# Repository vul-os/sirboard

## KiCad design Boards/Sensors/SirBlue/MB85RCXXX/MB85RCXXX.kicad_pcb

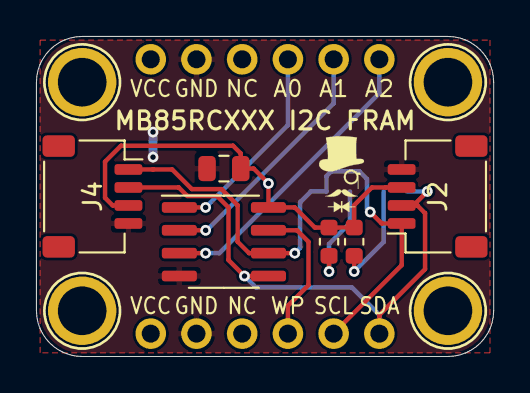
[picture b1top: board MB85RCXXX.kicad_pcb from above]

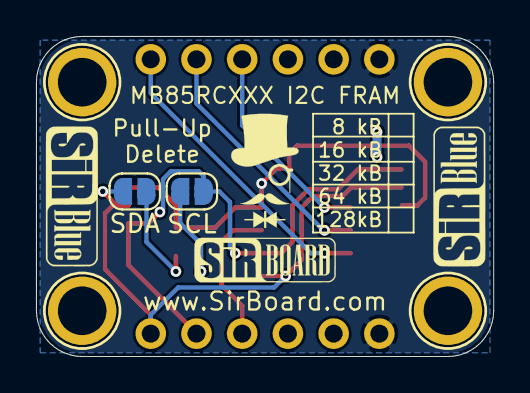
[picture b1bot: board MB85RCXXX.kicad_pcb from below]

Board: 2 copper layers, 25.4 x 17.8 mm, 14 parts (4 on the bottom side), 10 nets.

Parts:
C1: 10uF; C_0805_2012Metric
H1, H2, H3, H4: MountingHole; MountingHole_M2.5_SirBoard
J1, J3: Conn_01x06; PinHeader_1x06_P2.54mm_Vertical
J2, J4: Conn_01x04; JST_SH_SM04B-SRSS-TB_1x04-1MP_P1.00mm_Horizontal
R1, R2: 10K; R_0603_1608Metric
SCL: SolderJumper_2_Open; SolderJumper-2_P1.3mm_Open_RoundedPad1.0x1.5mm
SDA: SolderJumper_2_Open; SolderJumper-2_P1.3mm_Open_RoundedPad1.0x1.5mm
U1: MB85RCXXX; SOIC-8_3.9x4.9mm_P1.27mm

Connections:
A0: J3.4, U1.1
A1: J3.5, U1.2
A2: J3.6, U1.3
GND: C1.2, J1.2, J2.4, J3.2, J4.4, U1.4
unnamed: R1.2, SCL.2
unnamed: R2.2, SDA.2
SCL: J1.5, J2.1, J4.1, SCL.1, U1.6
SDA: J1.6, J2.2, J4.2, SDA.1, U1.5
VCC: C1.1, J1.1, J2.3, J3.1, J4.3, R1.1, R2.1, U1.8
WP: J1.4, U1.7

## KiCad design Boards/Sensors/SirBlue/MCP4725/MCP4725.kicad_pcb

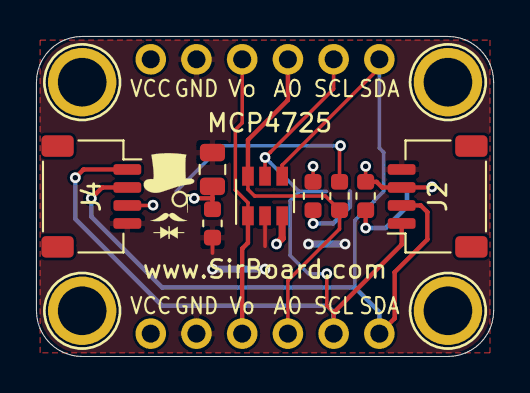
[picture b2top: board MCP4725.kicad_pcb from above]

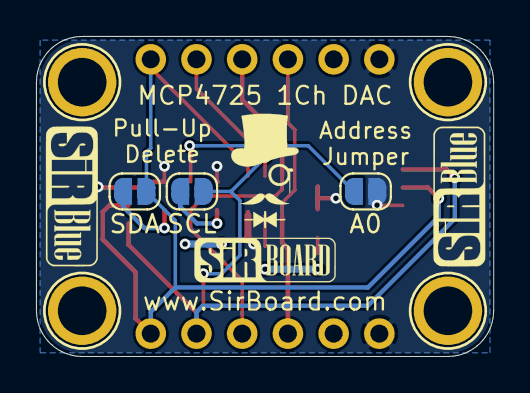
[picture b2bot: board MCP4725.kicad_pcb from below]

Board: 2 copper layers, 25.4 x 17.8 mm, 17 parts (5 on the bottom side), 9 nets.

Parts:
A0: SolderJumper_2_Open; SolderJumper-2_P1.3mm_Open_RoundedPad1.0x1.5mm
C1: 10uF; C_0805_2012Metric
C5: 100nF; C_0603_1608Metric
H1, H2, H3, H4: MountingHole; MountingHole_M2.5_SirBoard
J1, J3: Conn_01x06; PinHeader_1x06_P2.54mm_Vertical
J2, J4: Conn_01x04; JST_SH_SM04B-SRSS-TB_1x04-1MP_P1.00mm_Horizontal
R1, R2, R3: 10K; R_0603_1608Metric
SCL: SolderJumper_2_Open; SolderJumper-2_P1.3mm_Open_RoundedPad1.0x1.5mm
SDA: SolderJumper_2_Open; SolderJumper-2_P1.3mm_Open_RoundedPad1.0x1.5mm
U1: MCP4725; SOT-23-6

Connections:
A0: J1.4, J3.4, R3.2, U1.6
GND: C1.2, C5.2, J1.2, J2.4, J3.2, J4.4, U1.2
unnamed: A0.2, R3.1
unnamed: R1.2, SCL.2
unnamed: R2.2, SDA.2
SCL: J1.5, J2.1, J3.5, J4.1, SCL.1, U1.5
SDA: J1.6, J2.2, J3.6, J4.2, SDA.1, U1.4
VCC: A0.1, C1.1, C5.1, J1.1, J2.3, J3.1, J4.3, R1.1, R2.1, U1.3
Vout: J1.3, J3.3, U1.1

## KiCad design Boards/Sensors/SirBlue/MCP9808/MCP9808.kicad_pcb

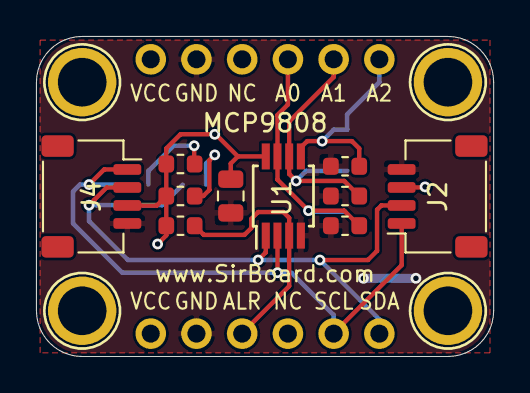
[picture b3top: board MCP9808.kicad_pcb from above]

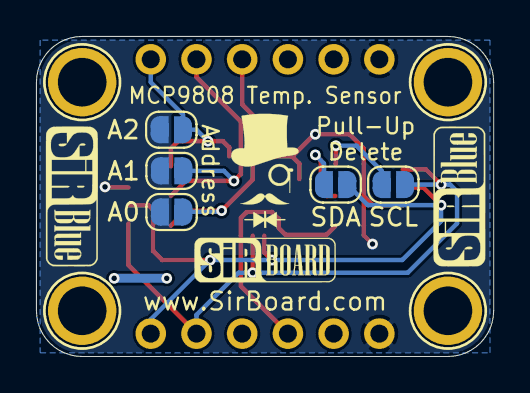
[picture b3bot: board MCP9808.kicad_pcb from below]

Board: 2 copper layers, 25.4 x 17.8 mm, 21 parts (7 on the bottom side), 10 nets.

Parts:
A0, A1, A2: SolderJumper_2_Open; SolderJumper-2_P1.3mm_Open_RoundedPad1.0x1.5mm
C1: 10uF; C_0805_2012Metric
H1, H2, H3, H4: MountingHole; MountingHole_M2.5_SirBoard
J1, J3: Conn_01x06; PinHeader_1x06_P2.54mm_Vertical
J2, J4: Conn_01x04; JST_SH_SM04B-SRSS-TB_1x04-1MP_P1.00mm_Horizontal
R1, R2, R3, R4, R5, R6: 10K; R_0603_1608Metric
SCL: SolderJumper_2_Open; SolderJumper-2_P1.3mm_Open_RoundedPad1.0x1.5mm
SDA: SolderJumper_2_Open; SolderJumper-2_P1.3mm_Open_RoundedPad1.0x1.5mm
U1: MCP9808_MSOP; MSOP-8_3x3mm_P0.65mm

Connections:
A0: A0.1, J3.4, R5.1, U1.7
A1: A1.1, J3.5, R4.1, U1.6
A2: A2.1, J3.6, R3.1, U1.5
ALERT: J1.3, R6.2, U1.3
GND: C1.2, J1.2, J2.4, J3.2, J4.4, R3.2, R4.2, R5.2, U1.4
unnamed: R1.2, SDA.2
unnamed: R2.2, SCL.2
SCL: J1.5, J2.1, J4.1, SCL.1, U1.2
SDA: J1.6, J2.2, J4.2, SDA.1, U1.1
VCC: A0.2, A1.2, A2.2, C1.1, J1.1, J2.3, J3.1, J4.3, R1.1, R2.1, R6.1, U1.8

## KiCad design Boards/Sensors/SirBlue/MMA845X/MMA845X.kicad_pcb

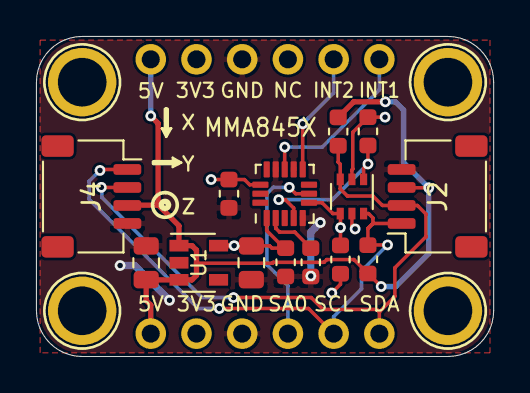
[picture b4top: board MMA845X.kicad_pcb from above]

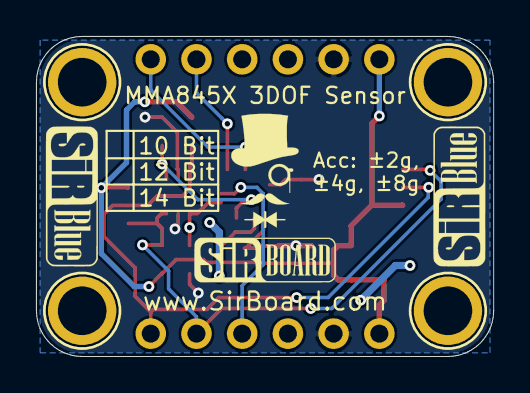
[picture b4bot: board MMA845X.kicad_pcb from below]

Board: 2 copper layers, 25.4 x 17.8 mm, 20 parts (2 on the bottom side), 11 nets.

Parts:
C1, C4: 10uF; C_0805_2012Metric
C2, C3, C5: 100nF; C_0603_1608Metric
H1, H2, H3, H4: MountingHole; MountingHole_M2.5_SirBoard
J1, J3: Conn_01x06; PinHeader_1x06_P2.54mm_Vertical
J2, J4: Conn_01x04; JST_SH_SM04B-SRSS-TB_1x04-1MP_P1.00mm_Horizontal
Q2: BSS138DW; SOT-363_SC-70-6
R5, R6, R7, R8: 10K; R_0603_1608Metric
U1: AP2127K-3.3; SOT-23-5
U2: MMA8451; QFN-COL-16-P=0.5

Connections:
3V3: C2.1, C4.1, C5.1, J1.2, J3.2, Q2.2, Q2.5, R5.2, R7.2, U1.5, U2.1, U2.14
5V: C1.1, J1.1, J2.3, J3.1, J4.3, R6.1, R8.1, U1.1, U1.3
GND: C1.2, C2.2, C3.2, C4.2, C5.2, J1.3, J2.4, J3.3, J4.4, U1.2, U2.5, U2.10, U2.12
INT1: J3.6, U2.11
INT2: J3.5, U2.9
unnamed: C3.1, U2.2
SA0: J1.4, U2.7
SCL_3V3: Q2.1, R5.1, U2.4
SCL_5V: J1.5, J2.1, J4.1, Q2.6, R6.2
SDA_3V3: Q2.4, R7.1, U2.6
SDA_5V: J1.6, J2.2, J4.2, Q2.3, R8.2

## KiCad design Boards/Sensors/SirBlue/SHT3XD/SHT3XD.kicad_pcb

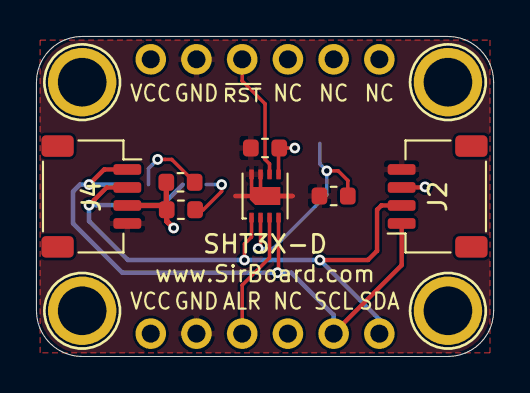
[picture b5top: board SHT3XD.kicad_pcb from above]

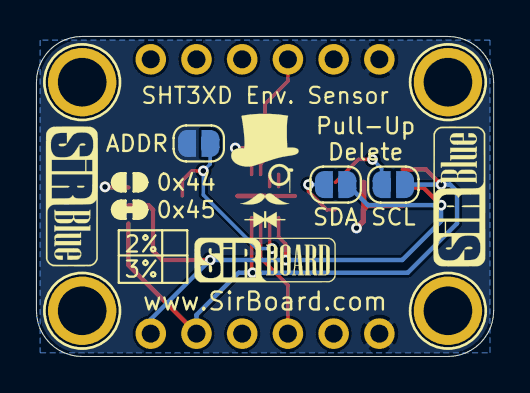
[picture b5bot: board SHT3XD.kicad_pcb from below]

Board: 2 copper layers, 25.4 x 17.8 mm, 16 parts (5 on the bottom side), 9 nets.

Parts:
ADDR: SolderJumper_2_Open; SolderJumper-2_P1.3mm_Open_RoundedPad1.0x1.5mm
C1: C; C_0603_1608Metric
H1, H2, H3, H4: MountingHole; MountingHole_M2.5_SirBoard
J1, J3: Conn_01x06; PinHeader_1x06_P2.54mm_Vertical
J2, J4: Conn_01x04; JST_SH_SM04B-SRSS-TB_1x04-1MP_P1.00mm_Horizontal
R1, R2, R3: 10K; R_0603_1608Metric
SCL: SolderJumper_2_Open; SolderJumper-2_P1.3mm_Open_RoundedPad1.0x1.5mm
SDA: SolderJumper_2_Open; SolderJumper-2_P1.3mm_Open_RoundedPad1.0x1.5mm
U1: SHT3X; DFN2.5X2.5_P=0.5m

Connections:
#RST: J3.3, U1.6
ALERT: J1.3, U1.3
GND: C1.2, J1.2, J2.4, J3.2, J4.4, R3.2, U1.7, U1.8, U1.9
unnamed: ADDR.1, R3.1, U1.2
unnamed: R1.2, SDA.2
unnamed: R2.2, SCL.2
SCL: J1.5, J2.1, J4.1, SCL.1, U1.4
SDA: J1.6, J2.2, J4.2, SDA.1, U1.1
VCC: ADDR.2, C1.1, J1.1, J2.3, J3.1, J4.3, R1.1, R2.1, U1.5

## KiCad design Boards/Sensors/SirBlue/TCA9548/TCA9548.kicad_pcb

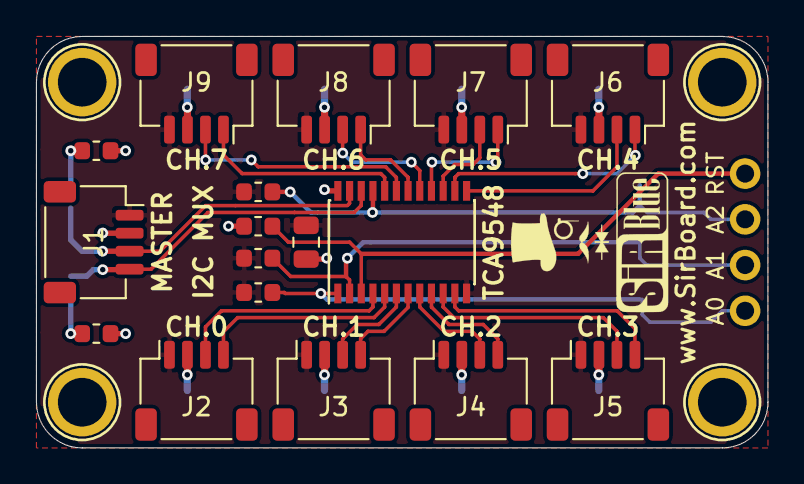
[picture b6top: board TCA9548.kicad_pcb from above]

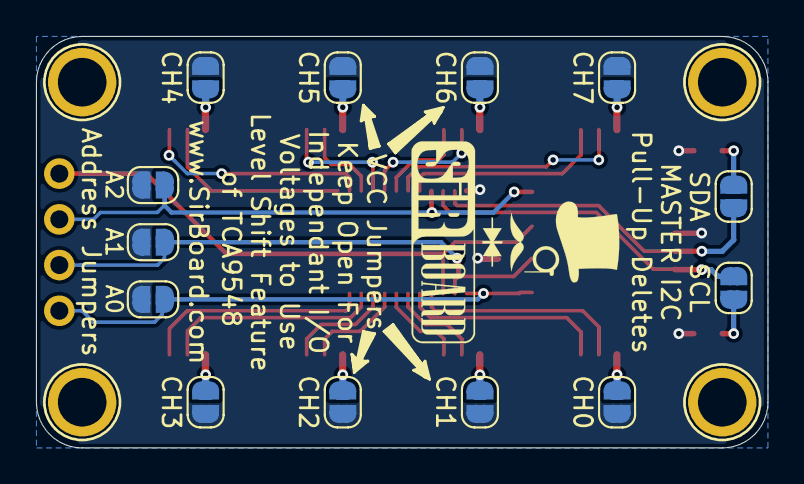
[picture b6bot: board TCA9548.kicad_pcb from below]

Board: 2 copper layers, 40.6 x 22.9 mm, 35 parts (13 on the bottom side), 34 nets.

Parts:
A0, A1, A2: SolderJumper_2_Open; SolderJumper-2_P1.3mm_Open_RoundedPad1.0x1.5mm
C1: 10uF; C_0805_2012Metric
CH0, CH1, CH2, CH3, CH4, CH5, CH6, CH7: SolderJumper_2_Open; SolderJumper-2_P1.3mm_Open_RoundedPad1.0x1.5mm
H1, H2, H3, H4: MountingHole; MountingHole_M2.5_SirBoard
J1, J2, J3, J4, J5, J6, J7, J8, J9: JST_SH_1mm; SirBlue_Connector
J10: 2.54mm; PinHeader_1x04_P2.54mm_Vertical
R1, R2, R3, R4, R5, R6: 10K; R_0603_1608Metric
SCL: SolderJumper_2_Open; SolderJumper-2_P1.3mm_Open_RoundedPad1.0x1.5mm
SDA: SolderJumper_2_Open; SolderJumper-2_P1.3mm_Open_RoundedPad1.0x1.5mm
TCA9548: TCA9548APWR; TSSOP-24_4.4x7.8mm_P0.65mm

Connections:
A0: A0.1, J10.4, R1.1, TCA9548.1
A1: A1.1, J10.3, R4.1, TCA9548.2
A2: A2.1, J10.2, R5.1, TCA9548.21
GND: C1.2, J1.1, J2.1, J3.1, J4.1, J5.1, J6.4, J7.4, J8.4, J9.4, R1.2, R4.2, R5.2, TCA9548.12
unnamed: CH0.2, J2.2
unnamed: CH1.2, J3.2
unnamed: CH2.2, J4.2
unnamed: CH3.2, J5.2
unnamed: CH4.2, J6.3
unnamed: CH5.2, J7.3
unnamed: CH6.2, J8.3
unnamed: CH7.2, J9.3
unnamed: R2.2, SCL.1
unnamed: R3.2, SDA.1
RST: J10.1, R6.2, TCA9548.3
SCL: J1.4, SCL.2, TCA9548.22
SCL0: J2.4, TCA9548.5
SCL1: J3.4, TCA9548.7
SCL2: J4.4, TCA9548.9
SCL3: J5.4, TCA9548.11
SCL4: J6.1, TCA9548.14
SCL5: J7.1, TCA9548.16
SCL6: J8.1, TCA9548.18
SCL7: J9.1, TCA9548.20
SDA: J1.3, SDA.2, TCA9548.23
SDA0: J2.3, TCA9548.4
SDA1: J3.3, TCA9548.6
SDA2: J4.3, TCA9548.8
SDA3: J5.3, TCA9548.10
SDA4: J6.2, TCA9548.13
SDA5: J7.2, TCA9548.15
SDA6: J8.2, TCA9548.17
SDA7: J9.2, TCA9548.19
VCC: A0.2, A1.2, A2.2, C1.1, CH0.1, CH1.1, CH2.1, CH3.1, CH4.1, CH5.1, CH6.1, CH7.1, J1.2, R2.1, R3.1, R6.1, TCA9548.24
